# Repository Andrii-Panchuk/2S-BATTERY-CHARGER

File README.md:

# 2S Battery Charger

USB-C powered charger for a 2-cell (2S) Li-ion battery pack, designed in
KiCad. The board requests a higher voltage from a USB-C Power Delivery
source (CH224K), charges the pack with a switching charger (MP26123) and
balances the two cells with a bleed-resistor circuit.

## Main components

| Ref | Part | Role |
|-----|------|------|
| J1 | SS-52400-002 | USB-C connector |
| F1 | 0ZCG0260FF2C | Resettable fuse on VBUS |
| U2 | CH224K | USB-C PD sink controller |
| U3 | USBLC6-2SC6 | ESD protection for USB data lines |
| U1 | MP26123 | 2-cell Li-ion switching charger |
| L1 | 4.7 µH | Buck inductor |
| D1, D4 | SS34 | Schottky diodes |
| R9 | 100 mΩ | Charge current sense |
| D2, D3 | LED | Charge status (CHGOK, ACOK) |
| SW1 | Push button | Connected to the EN pin of the charger |
| IC1, IC2 | HY2213-BB3A | Per-cell voltage detection for balancing |
| Q1, Q2 | AO3400A | Balancing switches |
| R13, R14 | 62 Ω | Balancing (bleed) resistors |
| J2 | 1x03 pin header | Battery: VBAT, BAT_MID, GND |

Full bill of materials: [`2S-BATTERY-CHARGER.csv`](2S-BATTERY-CHARGER.csv).

<p align="center"><em>2S battery charger: SS-52400-002, MP26123, CH224K, HY2213-BB3A and others components.</em></p>

## How It Works

### 1. Power Input & Protocol Negotiation
When a USB Type-C cable is connected:
* **Voltage Negotiation:** The **CH224K** trigger negotiates the required input voltage level with the power source (USB-PD / QC) to ensure high efficiency for the step-down converter.
* **Circuit Protection:** The VBUS line is protected against overcurrent by the **F1** resettable fuse (PPTC), while the DP/DM data lines are safeguarded against electrostatic discharge (ESD) using the **USBLC6-2SC6** diode array.

### 2. Three-Phase Charging Algorithm
The **MP26123** PWM switching charger implements a complete 3-phase charging cycle for a 2S Li-Ion/LiPo battery pack (up to 8.4V):
1. **Trickle / Pre-Charge Phase:** If the battery is deeply discharged (below the safe threshold), the controller applies a low, limited current to safely recover the cells without causing damage.
2. **Constant Current (CC) Phase:** Once the battery reaches nominal voltage, fast charging engages at full target current, set and regulated via the **R9** ($100\text{ m}\Omega$) current-sense resistor.
3. **Constant Voltage (CV) Phase:** As the total pack voltage reaches 8.4V, the controller holds the voltage constant while gradually reducing the charging current until the termination threshold is met.

### 3. Autonomous Passive Balancing
The cell balancer operates independently from the main charger IC to prevent individual cell overcharging:
* **IC1** and **IC2** (HY2213) continuously monitor the voltage of each section in the 2S series pack via the `BAT_MID` node.
* If either cell reaches its balancing threshold (~4.2V), its corresponding controller switches on the **AO3400A** N-channel MOSFET (Q1 or Q2).
* A bleed current of ~68 mA ($I = \frac{4.2\text{V}}{62\,\Omega}$) is dissipated as heat through the bleed resistor (**R13** or **R14**), slowing down the charging rate of the higher-voltage cell and allowing the lagging cell to catch up.

### 4. Control & Status Indication
* **Status LEDs:** The `CHGOK` and `ACOK` pins control status LEDs **D2/D3** to indicate power presence, active charging, and charge completion.
* **User Control:** Pushbutton **SW1** is connected to the charger's `EN` pin, allowing manual enable, disable, or reset of the charging process.

## PCB Design & Layout

### 1. Board Specifications
* **Layer Count:** 4-layer PCB (`F.Cu`, `In1.Cu`, `In2.Cu`, `B.Cu`).
* **Dimensions:** [66.67 mm × 30.7 mm]
* **Layer Stackup:**
  * **Top Layer (`F.Cu`):** Component placement, primary power traces, and high-frequency nodes.
  * **Inner Layer 1 (`In1.Cu`):** Solid Ground (GND) plane for low-impedance return paths and EMI shielding.
  * **Inner Layer 2 (`In2.Cu`):** Dedicated Power plane ($V_{BUS}$, $V_{BAT}$) for high-current delivery.
  * **Bottom Layer (`B.Cu`):** Secondary signal routing and thermal copper dissipation zones.

### 2. Component Placement Rationale
* **Logical Signal Flow:** Components are arranged linearly from left to right: USB-C input & ESD protection $\rightarrow$ PD trigger (CH224K) $\rightarrow$ Switching charger (MP26123) $\rightarrow$ Battery connector & passive balancer circuitry.
* **Minimized Switching Loop:** The inductor ($L_1$), freewheeling diode ($D_4$), and input/output capacitors ($C_4$, $C_{10}$) are placed immediately adjacent to $U_1$ (MP26123) to keep high-frequency power loops as short as possible.
* **Thermal Isolation:** The balancing bleed resistors ($R_{13}$, $R_{14}$) are placed near the battery connector, isolated from the sensitive control circuitry to prevent thermal drift.

### 3. Trace Widths & Power Routing
* **High-Current Paths ($V_{BUS}$, $V_{BAT}$, SW):** Routed with wide traces/copper fills ($\ge 1.0\text{ mm}$) to support charging currents up to 2A–3A with minimal DC resistance and voltage drop.
* **Switching (SW) Node:** Made short and wide to minimize parasitics and reduce radiated electromagnetic interference (EMI).
* **Sensitive Signals:** Signal traces for voltage feedback and USB DP/DM are routed with standard widths away from noisy power nodes.

### 4. Layout Challenges & Solutions
* **Noise Suppression:** To protect sensitive feedback ($COMP$, $V_{FB}$) lines from switching noise generated by $L_1$ and the SW node, the solid GND plane on `In1_Cu` acts as a shield between layers, and feedback traces are routed away from power loops.
* **Thermal Dissipation:** Thermal stitching vias are placed under the $U_1$ thermal pad and near balancing resistors ($R_{13}$, $R_{14}$) to transfer heat efficiently to internal power planes and the bottom layer.

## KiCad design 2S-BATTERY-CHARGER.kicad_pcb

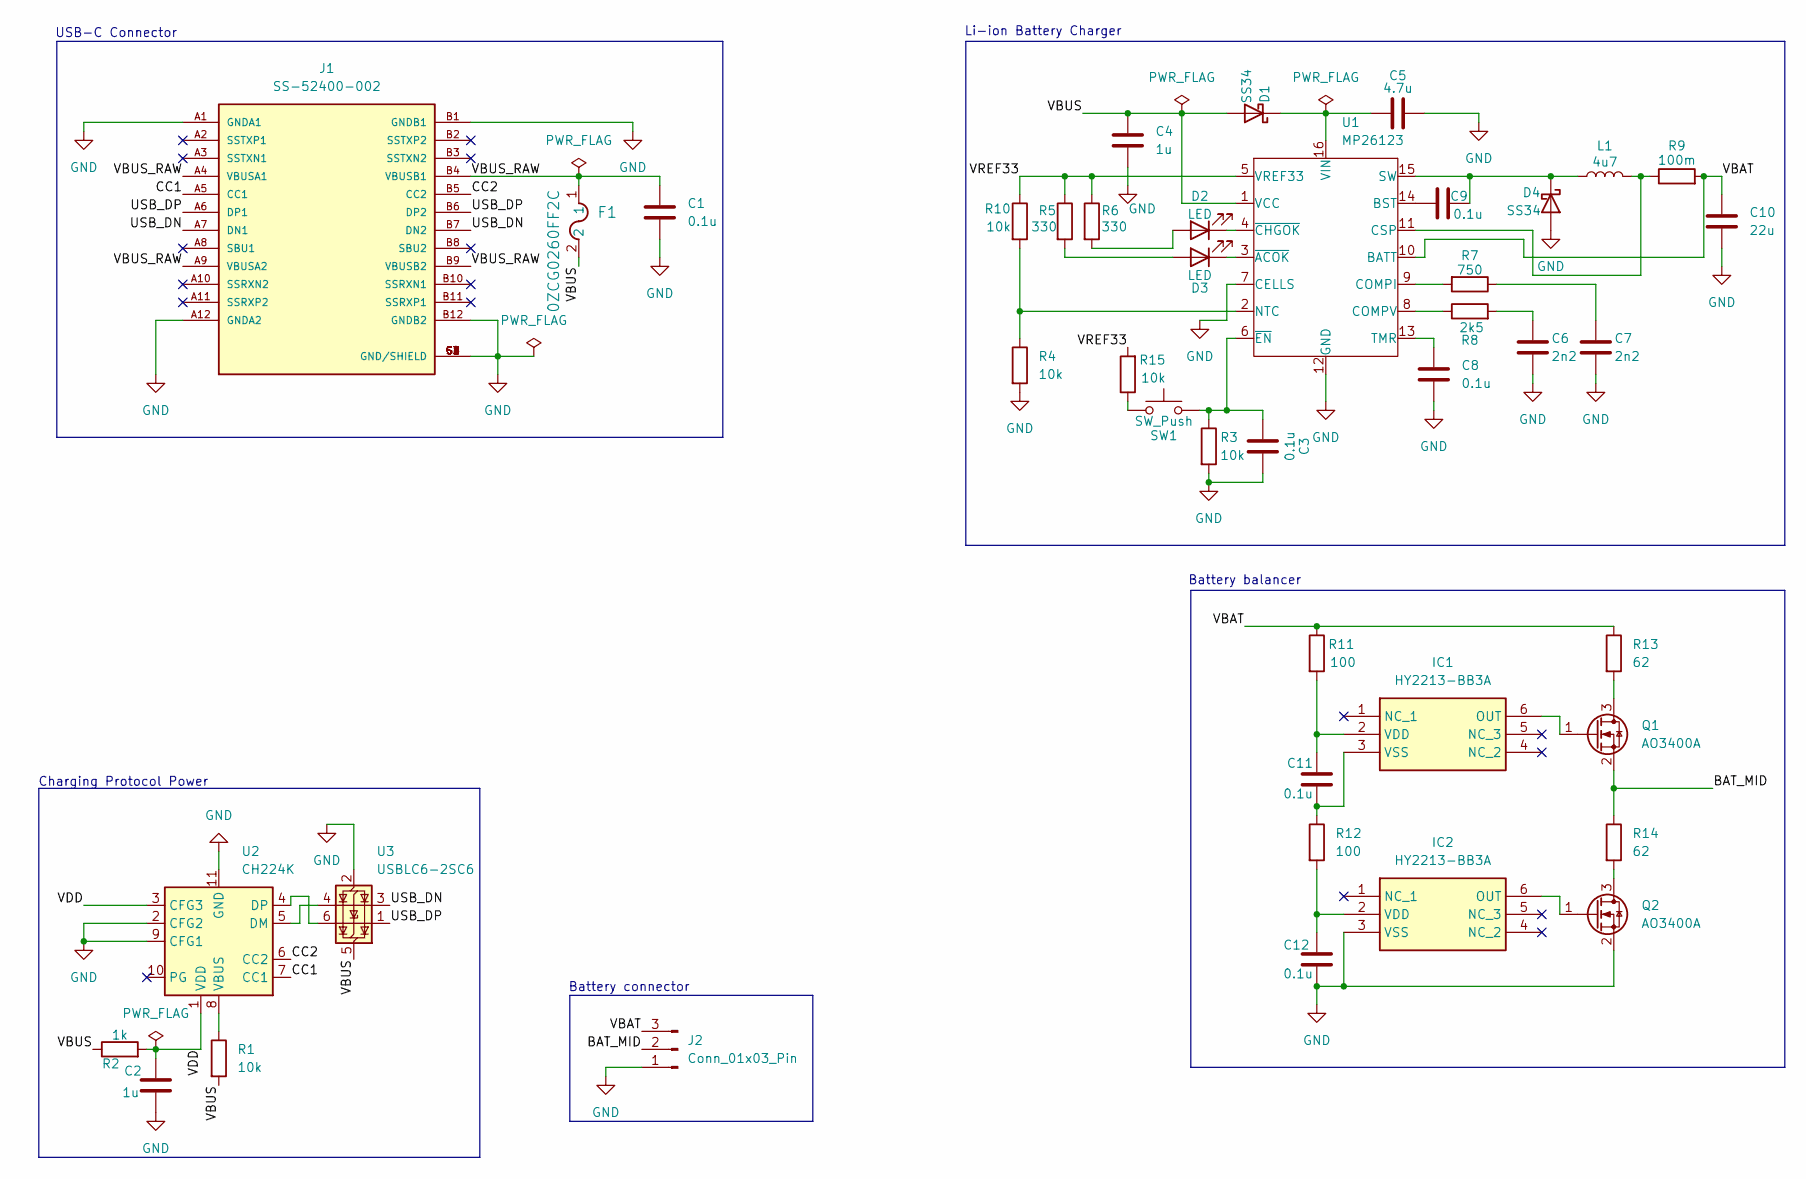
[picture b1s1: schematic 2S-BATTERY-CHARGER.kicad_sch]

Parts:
C1, C3, C8, C9, C11, C12: 0.1u; C_0805_2012Metric
C2, C4: 1u; C_0805_2012Metric
C5: 4.7u; C_1206_3216Metric
C6, C7: 2n2; C_0603_1608Metric
C10: 22u; C_1206_3216Metric
D1, D4: SS34; D_SMA
D2, D3: LED; LED_0805_2012Metric
F1: 0ZCG0260FF2C; Fuse_1812_4532Metric
IC1, IC2: HY2213-BB3A; SOT-23-6; Manufacturer_Part_Number HY2213-BB3A
J1: SS-52400-002; BELFUSE_SS-52400-002; PARTREV A0
J2: Conn_01x03_Pin; JST_EH_B3B-EH-A_1x03_P2.50mm_Vertical
L1: 4u7; L_7.3x7.3_H3.5
Q1, Q2: AO3400A; SOT-23
R1, R3, R4, R10, R15: 10k; R_0805_2012Metric
R2: 1k; R_0805_2012Metric
R5, R6: 330; R_0805_2012Metric
R7: 750; R_0805_2012Metric
R8: 2k5; R_0805_2012Metric
R9: 100m; R_1206_3216Metric
R11, R12: 100; R_0805_2012Metric
R13, R14: 62; R_1206_3216Metric
SW1: SW_Push; SW_SPST_TL3342
U1: MP26123; QFN-16-1EP_4x4mm_P0.65mm_EP2.5x2.5mm
U2: CH224K; SSOP-10-1EP_3.9x4.9mm_P1mm_EP2.1x3.3mm
U3: USBLC6-2SC6; SOT-23-6

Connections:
/BAT_MID: J2.2, Q1.2 (S), R14.1
/CC1: J1.A5 (CC1), U2.7 (CC1)
/CC2: J1.B5 (CC2), U2.6 (CC2)
/USB_DN: J1.A7 (DN1), J1.B7 (DN2), U3.3 (I/O2)
/USB_DP: J1.A6 (DP1), J1.B6 (DP2), U3.1 (I/O1)
/VBAT: C10.1, J2.3, R9.2, R11.1, R13.1, U1.10 (BATT)
/VBUS: C4.1, D1.2 (A), F1.2, R1.2, R2.1, U1.1 (VCC), U3.5 (VBUS)
/VBUS_RAW: C1.1, F1.1, J1.A4 (VBUSA1), J1.A9 (VBUSA2), J1.B4 (VBUSB1), J1.B9 (VBUSB2)
/VDD: C2.1, R2.2, U2.1 (VDD), U2.3 (CFG3)
/VREF33: R5.1, R6.1, R10.1, R15.2, U1.5 (VREF33)
GND: C1.2, C2.2, C3.2, C4.2, C5.2, C6.2, C7.2, C8.2, C10.2, C12.2, D4.2 (A), IC2.3 (VSS), J1.A1 (GNDA1), J1.A12 (GNDA2), J1.B1 (GNDB1), J1.B12 (GNDB2), J1.G1 (GND/SHIELD), J1.G2 (GND/SHIELD), J1.G3 (GND/SHIELD), J1.G4 (GND/SHIELD), J1.S1 (GND/SHIELD), J1.S2 (GND/SHIELD), J1.S3 (GND/SHIELD), J1.S4 (GND/SHIELD), J2.1, Q2.2 (S), R3.2, R4.2, U1.7 (CELLS), U1.12 (GND), U1.17, U2.2 (CFG2), U2.9 (CFG1), U2.11 (GND), U3.2 (GND)
unnamed: C6.1, R8.2
unnamed: C7.1, R7.1
unnamed: C5.1, D1.1 (K), U1.16 (VIN)
unnamed: D2.2 (A), R6.2
unnamed: D2.1 (K), U1.4 (~CHGOK)
unnamed: D3.2 (A), R5.2
unnamed: D3.1 (K), U1.3 (~ACOK)
unnamed: C9.1, D4.1 (K), L1.1, U1.15 (SW)
unnamed: IC1.6 (OUT), Q1.1 (G)
unnamed: C11.1, IC1.2 (VDD), R11.2
unnamed: C11.2, IC1.3 (VSS), R12.1
unnamed: IC2.6 (OUT), Q2.1 (G)
unnamed: C12.1, IC2.2 (VDD), R12.2
unnamed: Q1.3 (D), R13.2
unnamed: Q2.3 (D), R14.2
unnamed: R15.1, SW1.1
unnamed: C9.2, U1.14 (BST)
unnamed: R7.2, U1.9 (COMPI)
unnamed: R8.1, U1.8 (COMPV)
unnamed: L1.2, R9.1, U1.11 (CSP)
unnamed: R4.1, R10.2, U1.2 (NTC)
unnamed: C8.1, U1.13 (TMR)
unnamed: C3.1, R3.1, SW1.2, U1.6 (~EN)
unnamed: U2.5 (DM), U3.4 (I/O2)
unnamed: U2.4 (DP), U3.6 (I/O1)
unnamed: R1.1, U2.8 (VBUS)

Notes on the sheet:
Battery balancer
Li-ion Battery Charger
Charging Protocol Power
Battery connector
USB-C Connector

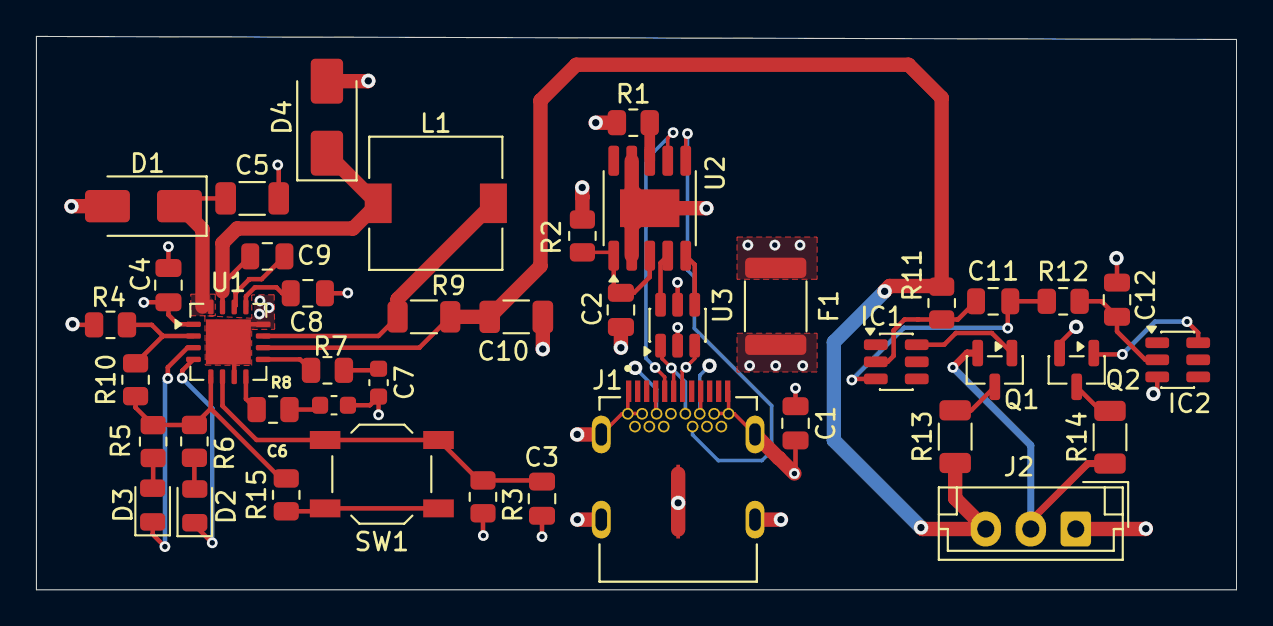
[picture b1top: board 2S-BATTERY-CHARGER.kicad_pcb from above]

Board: 4 copper layers, 66.7 x 30.7 mm, 43 parts (0 on the bottom side), 37 nets.
